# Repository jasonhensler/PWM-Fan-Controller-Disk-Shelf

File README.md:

# PWM-Fan-Controller-Disk-Shelf
Pwm fan controller and power adapter board for DIY Disk shelf using HP DL380P G8 12 x LFF cage and backplane. More details on the shelf are at https://forums.servethehome.com/index.php?threads/converting-an-hp-dl380e-gen8-14xlff-server-to-a-disk-shelf.29584/

Inputs:
* This board to accepts two PCI-E power connections to power the backplan and fans. 

Outputs:
* 2 PCI-E connectors to power the backplane itself 
* 6 4pin pwm fan connectors. The pwm signal is generated by a 555 timer and is adjustable.

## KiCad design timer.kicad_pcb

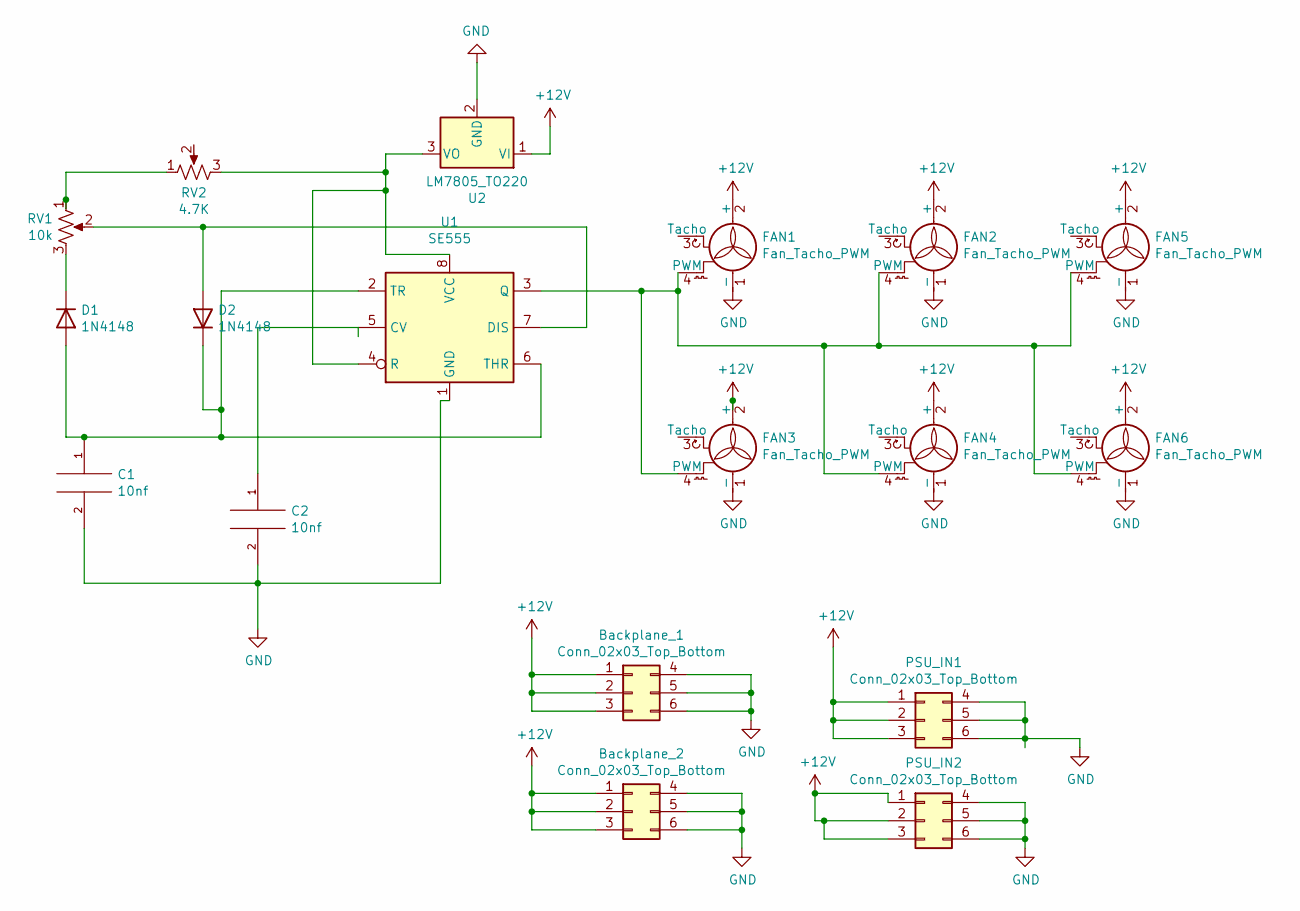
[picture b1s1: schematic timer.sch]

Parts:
Backplane_1, Backplane_2: Conn_02x03_Top_Bottom; Molex_Mini-Fit_Jr_5566-06A_2x03_P4.20mm_Vertical
C1, C2: 10nf; C_Disc_D4.7mm_W2.5mm_P5.00mm
D1, D2: 1N4148; D_DO-35_SOD27_P7.62mm_Horizontal
FAN1, FAN2, FAN3, FAN4, FAN5, FAN6: Fan_Tacho_PWM; PinHeader_1x04_P2.54mm_Vertical
PSU_IN1, PSU_IN2: Conn_02x03_Top_Bottom; Molex_Mini-Fit_Jr_5569-06A2_2x03_P4.20mm_Horizontal
RV1: 10k; Potentiometer_Piher_PT-10-H01_Horizontal
RV2: 4.7K; Potentiometer_Piher_PT-10-H01_Horizontal
U1: SE555; DIP-8_W7.62mm
U2: LM7805_TO220; TO-220-3_Vertical

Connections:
+12V: Backplane_1.1, Backplane_1.2, Backplane_1.3, Backplane_2.1, Backplane_2.2, Backplane_2.3, FAN1.2 (+), FAN2.2 (+), FAN3.2 (+), FAN4.2 (+), FAN5.2 (+), FAN6.2 (+), PSU_IN1.1, PSU_IN1.2, PSU_IN1.3, PSU_IN2.1, PSU_IN2.2, PSU_IN2.3, U2.1 (VI)
GND: Backplane_1.4, Backplane_1.5, Backplane_1.6, Backplane_2.4, Backplane_2.5, Backplane_2.6, C1.2, C2.2, FAN1.1 (-), FAN2.1 (-), FAN3.1 (-), FAN4.1 (-), FAN5.1 (-), FAN6.1 (-), PSU_IN1.4, PSU_IN1.5, PSU_IN1.6, PSU_IN2.4, PSU_IN2.5, PSU_IN2.6, U1.1 (GND), U2.2 (GND)
unnamed: C1.1, D1.2 (A), D2.1 (K), U1.2 (TR), U1.6 (THR)
unnamed: C2.1, U1.5 (CV)
unnamed: D1.1 (K), RV1.3
unnamed: D2.2 (A), RV1.2, U1.7 (DIS)
unnamed: FAN1.4 (PWM), FAN2.4 (PWM), FAN3.4 (PWM), FAN4.4 (PWM), FAN5.4 (PWM), FAN6.4 (PWM), U1.3 (Q)
unnamed: RV1.1, RV2.1
unnamed: RV2.3, U1.4 (R), U1.8 (VCC), U2.3 (VO)

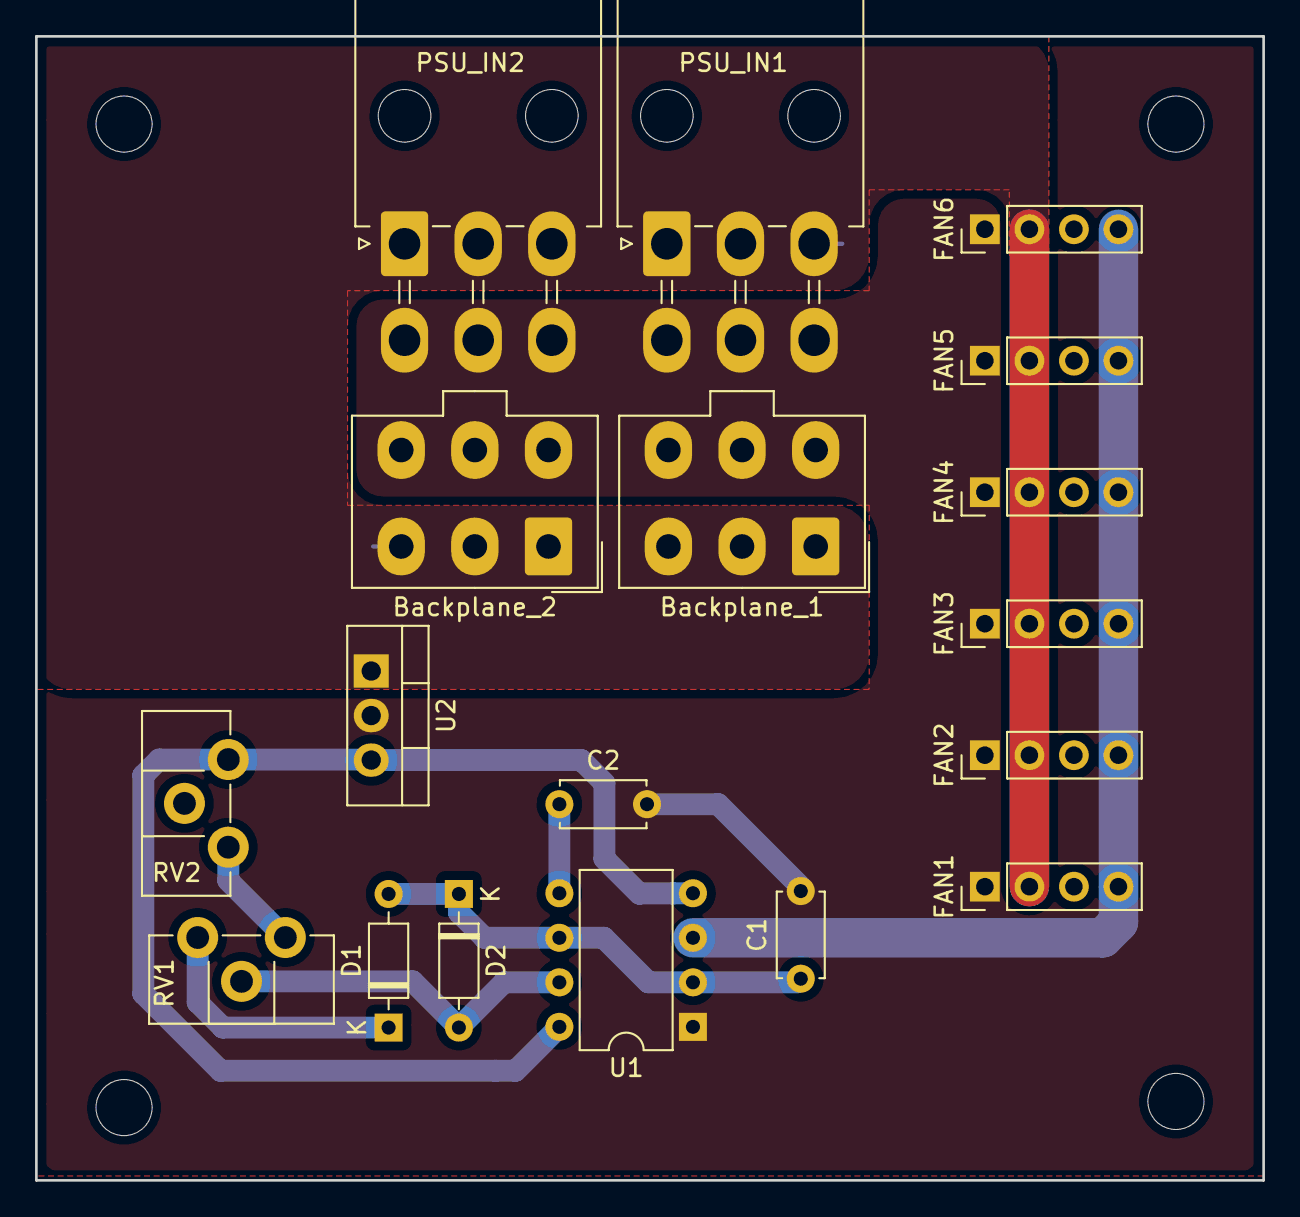
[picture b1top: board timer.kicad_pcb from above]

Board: 2 copper layers, 70.0 x 65.2 mm, 22 parts (0 on the bottom side), 9 nets.

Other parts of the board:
 : MountingHole_3.2mm_M3
 #2,  #3,  #4: MountingHole_3.2mm_M3

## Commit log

2021-05-31 Create LICENSE
2021-05-31 Inital public repo
